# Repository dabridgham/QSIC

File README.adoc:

= QSIC - QBUS Storage and I/O Card

The QSIC is a QBUS card with an FPGA and SD cards that emulates the old DEC disk
controllers and drives.

This repository is the KiCad project for the hardware, the QSIC board
itself.  In addition there are separate projects for a Unibus version
of the board, the http://github.com/dabridgham/USIC[USIC], the
http://github.com/dabridgham/QSIC-Verilog[Verilog code] that runs on
the FPGAs, and the code that runs on the embedded soft processor (not
yet started).

A companion http://github.com/dabridgham/Indicator-Panel[indicator
panel] is also available for those who want the blinkenlights.

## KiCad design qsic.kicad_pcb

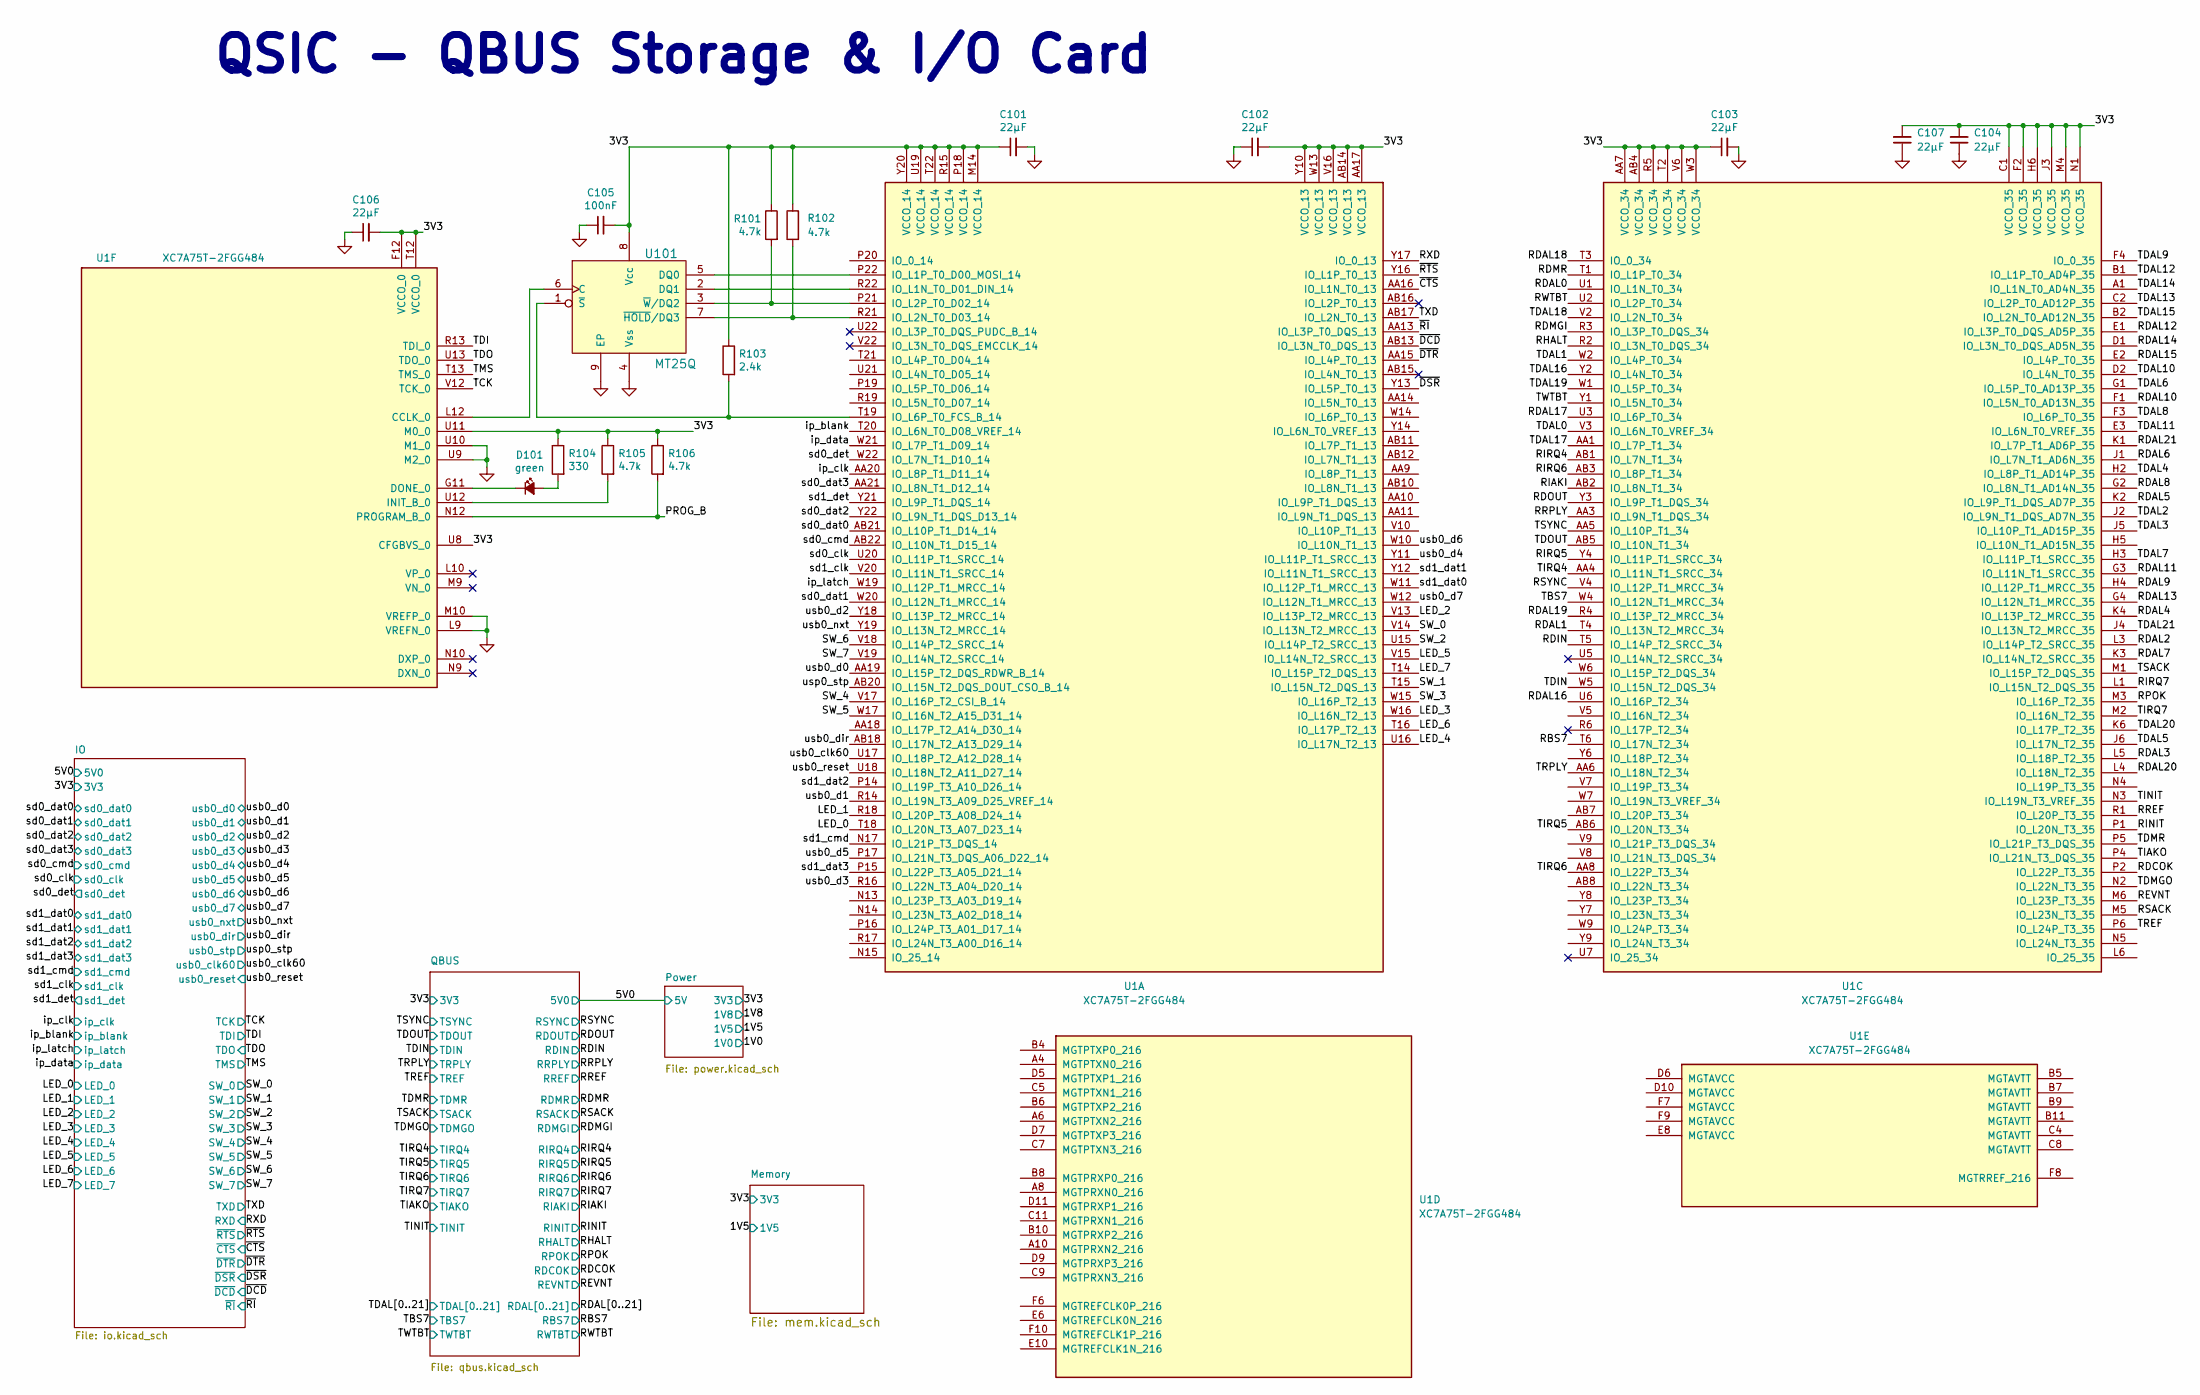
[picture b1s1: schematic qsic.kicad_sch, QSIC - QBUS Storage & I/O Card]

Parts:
C101, C102, C103, C104, C106, C107: 22µF; C_0603_1608Metric; MPN CL10A226MP8NUNE; JLCPCB Part C59461
C105: 100nF; C_0603_1608Metric; MPN CL10B104KO8NNNC
D101: green; LED_0603_1608Metric; MPN LTST-C190KGKT; JLCPCB Part C2297
R101, R102, R105, R106: 4.7k; R_0603_1608Metric; MPN RC0603FR-074K7L
R103: 2.4k; R_0603_1608Metric; MPN RC0603FR-072K4L
R104: 330; R_0603_1608Metric; MPN RC0603FR-07330RL
U1: XC7A75T-2FGG484; Xilinx_FGG484
U101: MT25Q; DFN-8-1EP_6x5mm_P1.27mm_EP4x4mm; MPN MT25QL128ABA1EW7-0SIT

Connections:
/3V3: C101.1, C102.2, C103.1, C104.2, C105.2, C106.2, C107.2, R101.1, R102.1, R103.1, R104.1, R105.1, R106.1, U1.AA7 (VCCO_34), U1.AA17 (VCCO_13), U1.AB4 (VCCO_34), U1.AB14 (VCCO_13), U1.C1 (VCCO_35), U1.F2 (VCCO_35), U1.F12 (VCCO_0), U1.H6 (VCCO_35), U1.J3 (VCCO_35), U1.M4 (VCCO_35), U1.M14 (VCCO_14), U1.N1 (VCCO_35), U1.P18 (VCCO_14), U1.R5 (VCCO_34), U1.R15 (VCCO_14), U1.T2 (VCCO_34), U1.T12 (VCCO_0), U1.T22 (VCCO_14), U1.U8 (CFGBVS_0), U1.U11 (M0_0), U1.U19 (VCCO_14), U1.V6 (VCCO_34), U1.V16 (VCCO_13), U1.W3 (VCCO_34), U1.W13 (VCCO_13), U1.Y10 (VCCO_13), U1.Y20 (VCCO_14), U101.8 (Vcc); also elsewhere on the board
/LED_0: U1.T18 (IO_L20N_T3_A07_D23_14); also elsewhere on the board
/LED_1: U1.R18 (IO_L20P_T3_A08_D24_14); also elsewhere on the board
/LED_2: U1.V13 (IO_L13P_T2_MRCC_13); also elsewhere on the board
/LED_3: U1.W16 (IO_L16N_T2_13); also elsewhere on the board
/LED_4: U1.U16 (IO_L17N_T2_13); also elsewhere on the board
/LED_5: U1.V15 (IO_L14N_T2_SRCC_13); also elsewhere on the board
/LED_6: U1.T16 (IO_L17P_T2_13); also elsewhere on the board
/LED_7: U1.T14 (IO_L15P_T2_DQS_13); also elsewhere on the board
/PROG_B: R106.2, U1.N12 (PROGRAM_B_0)
/RBS7: U1.T6 (IO_L17N_T2_34); also elsewhere on the board
/RDAL0: U1.U1 (IO_L1N_T0_34); also elsewhere on the board
/RDAL1: U1.T4 (IO_L13N_T2_MRCC_34); also elsewhere on the board
/RDAL2: U1.L3 (IO_L14P_T2_SRCC_35); also elsewhere on the board
/RDAL3: U1.L5 (IO_L18P_T2_35); also elsewhere on the board
/RDAL4: U1.K4 (IO_L13P_T2_MRCC_35); also elsewhere on the board
/RDAL5: U1.K2 (IO_L9P_T1_DQS_AD7P_35); also elsewhere on the board
/RDAL6: U1.J1 (IO_L7N_T1_AD6N_35); also elsewhere on the board
/RDAL7: U1.K3 (IO_L14N_T2_SRCC_35); also elsewhere on the board
/RDAL8: U1.G2 (IO_L8N_T1_AD14N_35); also elsewhere on the board
/RDAL9: U1.H4 (IO_L12P_T1_MRCC_35); also elsewhere on the board
/RDAL10: U1.F1 (IO_L5N_T0_AD13N_35); also elsewhere on the board
/RDAL11: U1.G3 (IO_L11N_T1_SRCC_35); also elsewhere on the board
/RDAL12: U1.E1 (IO_L3P_T0_DQS_AD5P_35); also elsewhere on the board
/RDAL13: U1.G4 (IO_L12N_T1_MRCC_35); also elsewhere on the board
/RDAL14: U1.D1 (IO_L3N_T0_DQS_AD5N_35); also elsewhere on the board
/RDAL15: U1.E2 (IO_L4P_T0_35); also elsewhere on the board
/RDAL16: U1.U6 (IO_L16P_T2_34); also elsewhere on the board
/RDAL17: U1.U3 (IO_L6P_T0_34); also elsewhere on the board
/RDAL18: U1.T3 (IO_0_34); also elsewhere on the board
/RDAL19: U1.R4 (IO_L13P_T2_MRCC_34); also elsewhere on the board
/RDAL20: U1.L4 (IO_L18N_T2_35); also elsewhere on the board
/RDAL21: U1.K1 (IO_L7P_T1_AD6P_35); also elsewhere on the board
/RDCOK: U1.P2 (IO_L22P_T3_35); also elsewhere on the board
/RDIN: U1.T5 (IO_L14P_T2_SRCC_34); also elsewhere on the board
/RDMGI: U1.R3 (IO_L3P_T0_DQS_34); also elsewhere on the board
/RDMR: U1.T1 (IO_L1P_T0_34); also elsewhere on the board
/RDOUT: U1.Y3 (IO_L9P_T1_DQS_34); also elsewhere on the board
/REVNT: U1.M6 (IO_L23P_T3_35); also elsewhere on the board
/RHALT: U1.R2 (IO_L3N_T0_DQS_34); also elsewhere on the board
/RIAKI: U1.AB2 (IO_L8N_T1_34); also elsewhere on the board
/RINIT: U1.P1 (IO_L20N_T3_35); also elsewhere on the board
/RIRQ4: U1.AB1 (IO_L7N_T1_34); also elsewhere on the board
/RIRQ5: U1.Y4 (IO_L11P_T1_SRCC_34); also elsewhere on the board
/RIRQ6: U1.AB3 (IO_L8P_T1_34); also elsewhere on the board
/RIRQ7: U1.L1 (IO_L15N_T2_DQS_35); also elsewhere on the board
/RPOK: U1.M3 (IO_L16P_T2_35); also elsewhere on the board
/RREF: U1.R1 (IO_L20P_T3_35); also elsewhere on the board
/RRPLY: U1.AA3 (IO_L9N_T1_DQS_34); also elsewhere on the board
/RSACK: U1.M5 (IO_L23N_T3_35); also elsewhere on the board
/RSYNC: U1.V4 (IO_L12P_T1_MRCC_34); also elsewhere on the board
/RWTBT: U1.U2 (IO_L2P_T0_34); also elsewhere on the board
/RXD: U1.Y17 (IO_0_13); also elsewhere on the board
/SW_0: U1.V14 (IO_L13N_T2_MRCC_13); also elsewhere on the board
/SW_1: U1.T15 (IO_L15N_T2_DQS_13); also elsewhere on the board
/SW_2: U1.U15 (IO_L14P_T2_SRCC_13); also elsewhere on the board
/SW_3: U1.W15 (IO_L16P_T2_13); also elsewhere on the board
/SW_4: U1.V17 (IO_L16P_T2_CSI_B_14); also elsewhere on the board
/SW_5: U1.W17 (IO_L16N_T2_A15_D31_14); also elsewhere on the board
/SW_6: U1.V18 (IO_L14P_T2_SRCC_14); also elsewhere on the board
/SW_7: U1.V19 (IO_L14N_T2_SRCC_14); also elsewhere on the board
/TBS7: U1.W4 (IO_L12N_T1_MRCC_34); also elsewhere on the board
/TCK: U1.V12 (TCK_0); also elsewhere on the board
/TDAL0: U1.V3 (IO_L6N_T0_VREF_34); also elsewhere on the board
/TDAL1: U1.W2 (IO_L4P_T0_34); also elsewhere on the board
/TDAL2: U1.J2 (IO_L9N_T1_DQS_AD7N_35); also elsewhere on the board
/TDAL3: U1.J5 (IO_L10P_T1_AD15P_35); also elsewhere on the board
/TDAL4: U1.H2 (IO_L8P_T1_AD14P_35); also elsewhere on the board
/TDAL5: U1.J6 (IO_L17N_T2_35); also elsewhere on the board
/TDAL6: U1.G1 (IO_L5P_T0_AD13P_35); also elsewhere on the board
/TDAL7: U1.H3 (IO_L11P_T1_SRCC_35); also elsewhere on the board
/TDAL8: U1.F3 (IO_L6P_T0_35); also elsewhere on the board
/TDAL9: U1.F4 (IO_0_35); also elsewhere on the board
/TDAL10: U1.D2 (IO_L4N_T0_35); also elsewhere on the board
/TDAL11: U1.E3 (IO_L6N_T0_VREF_35); also elsewhere on the board
/TDAL12: U1.B1 (IO_L1P_T0_AD4P_35); also elsewhere on the board
/TDAL13: U1.C2 (IO_L2P_T0_AD12P_35); also elsewhere on the board
/TDAL14: U1.A1 (IO_L1N_T0_AD4N_35); also elsewhere on the board
/TDAL15: U1.B2 (IO_L2N_T0_AD12N_35); also elsewhere on the board
/TDAL16: U1.Y2 (IO_L4N_T0_34); also elsewhere on the board
/TDAL17: U1.AA1 (IO_L7P_T1_34); also elsewhere on the board
/TDAL18: U1.V2 (IO_L2N_T0_34); also elsewhere on the board
/TDAL19: U1.W1 (IO_L5P_T0_34); also elsewhere on the board
/TDAL20: U1.K6 (IO_L17P_T2_35); also elsewhere on the board
/TDAL21: U1.J4 (IO_L13N_T2_MRCC_35); also elsewhere on the board
/TDI: U1.R13 (TDI_0); also elsewhere on the board
/TDIN: U1.W5 (IO_L15N_T2_DQS_34); also elsewhere on the board
/TDMGO: U1.N2 (IO_L22N_T3_35)
/TDMR: U1.P5 (IO_L21P_T3_DQS_35); also elsewhere on the board
/TDO: U1.U13 (TDO_0); also elsewhere on the board
/TDOUT: U1.AB5 (IO_L10N_T1_34); also elsewhere on the board
/TIAKO: U1.P4 (IO_L21N_T3_DQS_35); also elsewhere on the board
/TINIT: U1.N3 (IO_L19N_T3_VREF_35); also elsewhere on the board
/TIRQ4: U1.AA4 (IO_L11N_T1_SRCC_34); also elsewhere on the board
/TIRQ5: U1.AB6 (IO_L20N_T3_34); also elsewhere on the board
/TIRQ6: U1.AA8 (IO_L22P_T3_34); also elsewhere on the board
/TIRQ7: U1.M2 (IO_L16N_T2_35); also elsewhere on the board
/TMS: U1.T13 (TMS_0); also elsewhere on the board
/TREF: U1.P6 (IO_L24P_T3_35)
/TRPLY: U1.AA6 (IO_L18N_T2_34); also elsewhere on the board
/TSACK: U1.M1 (IO_L15P_T2_DQS_35); also elsewhere on the board
/TSYNC: U1.AA5 (IO_L10P_T1_34); also elsewhere on the board
/TWTBT: U1.Y1 (IO_L5N_T0_34); also elsewhere on the board
/TXD: U1.AB17 (IO_L2N_T0_13); also elsewhere on the board
/ip_blank: U1.T20 (IO_L6N_T0_D08_VREF_14); also elsewhere on the board
/ip_clk: U1.AA20 (IO_L8P_T1_D11_14); also elsewhere on the board
/ip_data: U1.W21 (IO_L7P_T1_D09_14); also elsewhere on the board
/ip_latch: U1.W19 (IO_L12P_T1_MRCC_14); also elsewhere on the board
/sd0_clk: U1.U20 (IO_L11P_T1_SRCC_14); also elsewhere on the board
/sd0_cmd: U1.AB22 (IO_L10N_T1_D15_14); also elsewhere on the board
/sd0_dat0: U1.AB21 (IO_L10P_T1_D14_14); also elsewhere on the board
/sd0_dat1: U1.W20 (IO_L12N_T1_MRCC_14); also elsewhere on the board
/sd0_dat2: U1.Y22 (IO_L9N_T1_DQS_D13_14); also elsewhere on the board
/sd0_dat3: U1.AA21 (IO_L8N_T1_D12_14); also elsewhere on the board
/sd0_det: U1.W22 (IO_L7N_T1_D10_14); also elsewhere on the board
/sd1_clk: U1.V20 (IO_L11N_T1_SRCC_14); also elsewhere on the board
/sd1_cmd: U1.N17 (IO_L21P_T3_DQS_14); also elsewhere on the board
/sd1_dat0: U1.W11 (IO_L12P_T1_MRCC_13); also elsewhere on the board
/sd1_dat1: U1.Y12 (IO_L11N_T1_SRCC_13); also elsewhere on the board
/sd1_dat2: U1.P14 (IO_L19P_T3_A10_D26_14); also elsewhere on the board
/sd1_dat3: U1.P15 (IO_L22P_T3_A05_D21_14); also elsewhere on the board
/sd1_det: U1.Y21 (IO_L9P_T1_DQS_14); also elsewhere on the board
/usb0_clk60: U1.U17 (IO_L18P_T2_A12_D28_14); also elsewhere on the board
/usb0_d0: U1.AA19 (IO_L15P_T2_DQS_RDWR_B_14); also elsewhere on the board
/usb0_d1: U1.R14 (IO_L19N_T3_A09_D25_VREF_14); also elsewhere on the board
/usb0_d2: U1.Y18 (IO_L13P_T2_MRCC_14); also elsewhere on the board
/usb0_d3: U1.R16 (IO_L22N_T3_A04_D20_14); also elsewhere on the board
/usb0_d4: U1.Y11 (IO_L11P_T1_SRCC_13); also elsewhere on the board
/usb0_d5: U1.P17 (IO_L21N_T3_DQS_A06_D22_14); also elsewhere on the board
/usb0_d6: U1.W10 (IO_L10N_T1_13); also elsewhere on the board
/usb0_d7: U1.W12 (IO_L12N_T1_MRCC_13); also elsewhere on the board
/usb0_dir: U1.AB18 (IO_L17N_T2_A13_D29_14); also elsewhere on the board
/usb0_nxt: U1.Y19 (IO_L13N_T2_MRCC_14); also elsewhere on the board
/usb0_reset: U1.U18 (IO_L18N_T2_A11_D27_14); also elsewhere on the board
/usp0_stp: U1.AB20 (IO_L15N_T2_DQS_DOUT_CSO_B_14); also elsewhere on the board
/~CTS: U1.AA16 (IO_L1N_T0_13); also elsewhere on the board
/~DCD: U1.AB13 (IO_L3N_T0_DQS_13); also elsewhere on the board
/~DSR: U1.Y13 (IO_L5P_T0_13); also elsewhere on the board
/~DTR: U1.AA15 (IO_L4P_T0_13); also elsewhere on the board
/~RI: U1.AA13 (IO_L3P_T0_DQS_13); also elsewhere on the board
/~RTS: U1.Y16 (IO_L1P_T0_13); also elsewhere on the board
GND: C101.2, C102.1, C103.2, C104.1, C105.1, C106.1, C107.1, U1.L9 (VREFN_0), U1.M10 (VREFP_0), U1.U9 (M2_0), U1.U10 (M1_0), U101.4 (Vss), U101.9 (EP); also elsewhere on the board
unnamed: D101.2 (A), R104.2
unnamed: D101.1 (K), U1.G11 (DONE_0)
unnamed: R105.2, U1.U12 (INIT_B_0)
unnamed: U1.L12 (CCLK_0), U101.6 (C)
unnamed: U1.P22 (IO_L1P_T0_D00_MOSI_14), U101.5 (DQ0)
unnamed: U1.R22 (IO_L1N_T0_D01_DIN_14), U101.2 (DQ1)
unnamed: R102.2, U1.R21 (IO_L2N_T0_D03_14), U101.7 (~HOLD/DQ3)
unnamed: R103.2, U1.T19 (IO_L6P_T0_FCS_B_14), U101.1 (~S)
unnamed: R101.2, U1.P21 (IO_L2P_T0_D02_14), U101.3 (~W/DQ2)

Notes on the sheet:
QSIC - QBUS Storage & I/O Card

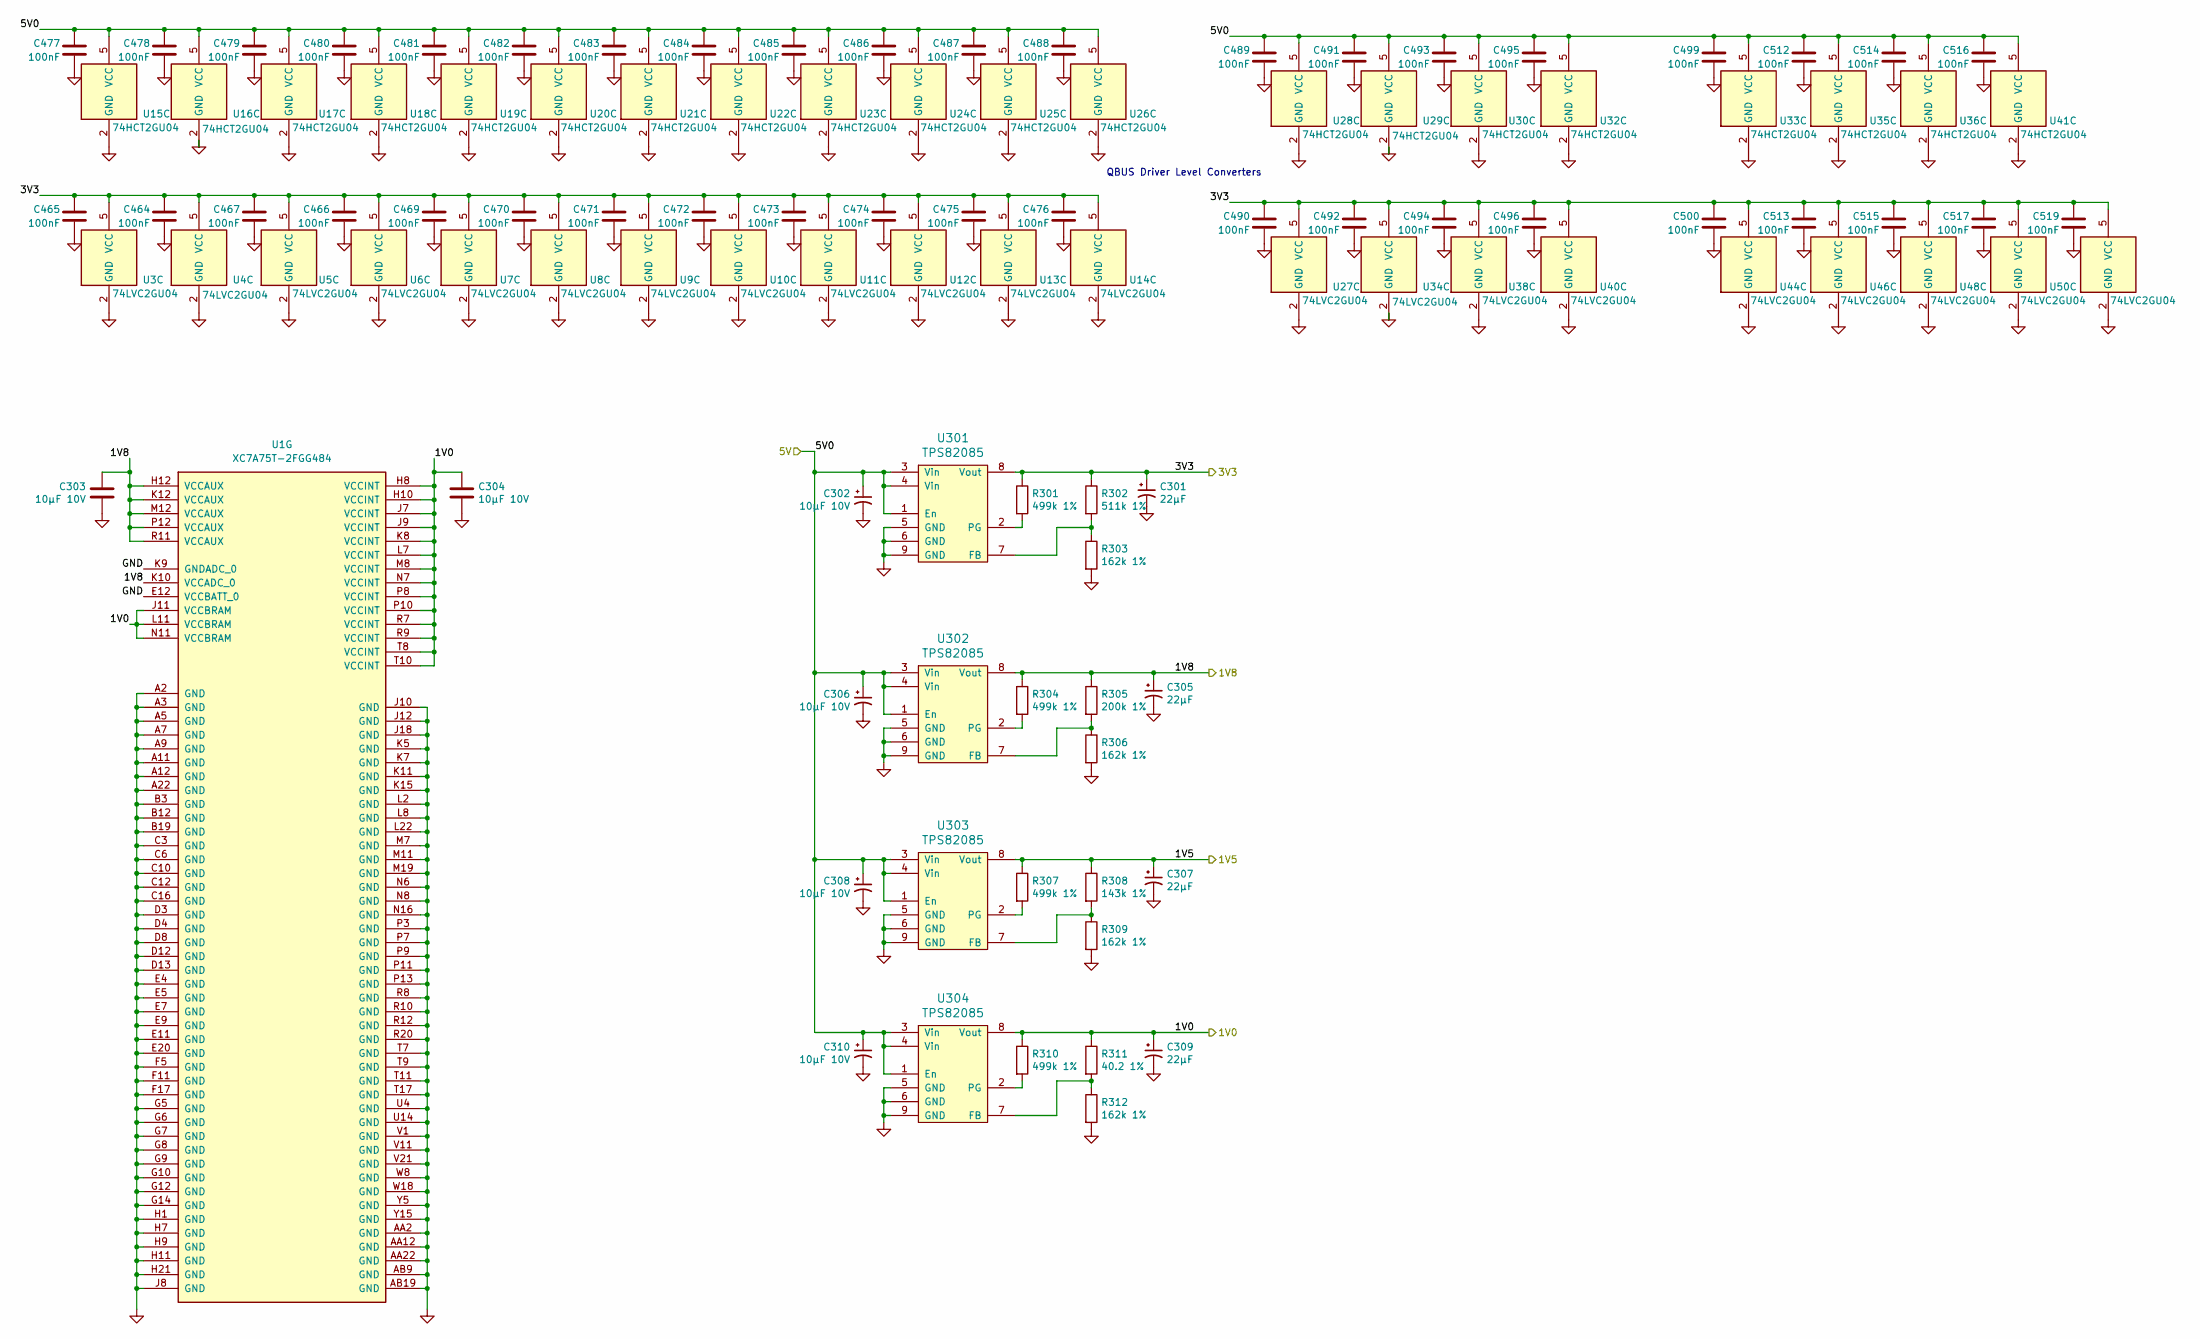
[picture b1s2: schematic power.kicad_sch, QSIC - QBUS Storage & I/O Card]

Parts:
C301, C305, C307, C309: 22µF; C_0603_1608Metric; MPN CL10A226MP8NUNE; JLCPCB Part C59461
C302, C303, C304, C306, C308, C310: 10µF 10V; C_0603_1608Metric; MPN CL10A106MP8NNNC; JLCPCB Part C85713
C464, C465, C466, C467, C469, C470, C471, C472, C473, C474, C475, C476, C477, C478, C479, C480, C481, C482, C483, C484, C485, C486, C487, C488, C489, C490, C491, C492, C493, C494, C495, C496, C499, C500, C512, C513, C514, C515, C516, C517, C519: 100nF; C_0402_1005Metric
R301, R304, R307, R310: 499k 1%; R_0603_1608Metric; MPN RC0603FR-07499KL; JLCPCB Part C131054
R302: 511k 1%; R_0603_1608Metric; MPN RC0603FR-07511KL; JLCPCB Part C188257
R303, R306, R309, R312: 162k 1%; R_0603_1608Metric; MPN RC0603FR-07162KL
R305: 200k 1%; R_0603_1608Metric; MPN RC0603FR-07200KL
R308: 143k 1%; R_0603_1608Metric; MPN RC0603FR-07143KL
R311: 40.2 1%; R_0603_1608Metric; MPN RC0603FR-0740R2L
U1: XC7A75T-2FGG484; Xilinx_FGG484
U3, U4, U5, U6, U7, U8, U9, U10, U11, U12, U13, U14, U27, U34, U38, U40, U44, U46, U48, U50, U52: 74LVC2GU04; SOT-363_SC-70-6
U15, U16, U17, U18, U19, U20, U21, U22, U23, U24, U25, U26, U28, U29, U30, U32, U33, U35, U36, U41: 74HCT2GU04; SOT-363_SC-70-6
U301, U302, U303, U304: TPS82085; Texas_SIL0008D_MicroSiP-8-1EP_2.8x3mm_P0.65mm_EP1.1x1.9mm_T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; MPN TPS82085SILT

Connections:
/1V0: C304.1, C309.1, R310.1, R311.1, U1.H8 (VCCINT), U1.H10 (VCCINT), U1.J7 (VCCINT), U1.J9 (VCCINT), U1.J11 (VCCBRAM), U1.K8 (VCCINT), U1.L7 (VCCINT), U1.L11 (VCCBRAM), U1.M8 (VCCINT), U1.N7 (VCCINT), U1.N11 (VCCBRAM), U1.P8 (VCCINT), U1.P10 (VCCINT), U1.R7 (VCCINT), U1.R9 (VCCINT), U1.T8 (VCCINT), U1.T10 (VCCINT), U304.8 (Vout)
/1V5: C307.1, R307.1, R308.1, U303.8 (Vout); also elsewhere on the board
/1V8: C303.1, C305.1, R304.1, R305.1, U1.H12 (VCCAUX), U1.K10 (VCCADC_0), U1.K12 (VCCAUX), U1.M12 (VCCAUX), U1.P12 (VCCAUX), U1.R11 (VCCAUX), U302.8 (Vout)
/3V3: C301.1, C464.1, C465.1, C466.1, C467.1, C469.1, C470.1, C471.1, C472.1, C473.1, C474.1, C475.1, C476.1, C490.1, C492.1, C494.1, C496.1, C500.1, C513.1, C515.1, C517.1, C519.1, R301.1, R302.1, U3.5 (VCC), U4.5 (VCC), U5.5 (VCC), U6.5 (VCC), U7.5 (VCC), U8.5 (VCC), U9.5 (VCC), U10.5 (VCC), U11.5 (VCC), U12.5 (VCC), U13.5 (VCC), U14.5 (VCC), U27.5 (VCC), U34.5 (VCC), U38.5 (VCC), U40.5 (VCC), U44.5 (VCC), U46.5 (VCC), U48.5 (VCC), U50.5 (VCC), U52.5 (VCC), U301.8 (Vout); also elsewhere on the board
/5V0: C302.1, C306.1, C308.1, C310.1, C477.1, C478.1, C479.1, C480.1, C481.1, C482.1, C483.1, C484.1, C485.1, C486.1, C487.1, C488.1, C489.1, C491.1, C493.1, C495.1, C499.1, C512.1, C514.1, C516.1, U15.5 (VCC), U16.5 (VCC), U17.5 (VCC), U18.5 (VCC), U19.5 (VCC), U20.5 (VCC), U21.5 (VCC), U22.5 (VCC), U23.5 (VCC), U24.5 (VCC), U25.5 (VCC), U26.5 (VCC), U28.5 (VCC), U29.5 (VCC), U30.5 (VCC), U32.5 (VCC), U33.5 (VCC), U35.5 (VCC), U36.5 (VCC), U41.5 (VCC), U301.1 (En), U301.3 (Vin), U301.4 (Vin), U302.1 (En), U302.3 (Vin), U302.4 (Vin), U303.1 (En), U303.3 (Vin), U303.4 (Vin), U304.1 (En), U304.3 (Vin), U304.4 (Vin); also elsewhere on the board
GND: C301.2, C302.2, C303.2, C304.2, C305.2, C306.2, C307.2, C308.2, C309.2, C310.2, C464.2, C465.2, C466.2, C467.2, C469.2, C470.2, C471.2, C472.2, C473.2, C474.2, C475.2, C476.2, C477.2, C478.2, C479.2, C480.2, C481.2, C482.2, C483.2, C484.2, C485.2, C486.2, C487.2, C488.2, C489.2, C490.2, C491.2, C492.2, C493.2, C494.2, C495.2, C496.2, C499.2, C500.2, C512.2, C513.2, C514.2, C515.2, C516.2, C517.2, C519.2, R303.2, R306.2, R309.2, R312.2, U1.A2 (GND), U1.A3 (GND), U1.A5 (GND), U1.A7 (GND), U1.A9 (GND), U1.A11 (GND), U1.A12 (GND), U1.A22 (GND), U1.AA2 (GND), U1.AA12 (GND), U1.AA22 (GND), U1.AB9 (GND), U1.AB19 (GND), U1.B3 (GND), U1.B12 (GND), U1.B19 (GND), U1.C3 (GND), U1.C6 (GND), U1.C10 (GND), U1.C12 (GND), U1.C16 (GND), U1.D3 (GND), U1.D4 (GND), U1.D8 (GND), U1.D12 (GND), U1.D13 (GND), U1.E4 (GND), U1.E5 (GND), U1.E7 (GND), U1.E9 (GND), U1.E11 (GND), U1.E12 (VCCBATT_0), U1.E20 (GND), U1.F5 (GND), U1.F11 (GND), U1.F17 (GND), U1.G5 (GND), U1.G6 (GND), U1.G7 (GND), U1.G8 (GND), U1.G9 (GND), U1.G10 (GND), U1.G12 (GND), U1.G14 (GND), U1.H1 (GND), U1.H7 (GND), U1.H9 (GND), U1.H11 (GND), U1.H21 (GND), U1.J8 (GND), U1.J10 (GND), U1.J12 (GND), U1.J18 (GND), U1.K5 (GND), U1.K7 (GND), U1.K9 (GNDADC_0), U1.K11 (GND), U1.K15 (GND), U1.L2 (GND), U1.L8 (GND), U1.L22 (GND), U1.M7 (GND), U1.M11 (GND), U1.M19 (GND), U1.N6 (GND), U1.N8 (GND), U1.N16 (GND), U1.P3 (GND), U1.P7 (GND), U1.P9 (GND), U1.P11 (GND), U1.P13 (GND), U1.R8 (GND), U1.R10 (GND), U1.R12 (GND), U1.R20 (GND), U1.T7 (GND), U1.T9 (GND), U1.T11 (GND), U1.T17 (GND), U1.U4 (GND), U1.U14 (GND), U1.V1 (GND), U1.V11 (GND), U1.V21 (GND), U1.W8 (GND), U1.W18 (GND), U1.Y5 (GND), U1.Y15 (GND), U3.2 (GND), U4.2 (GND), U5.2 (GND), U6.2 (GND), U7.2 (GND), U8.2 (GND), U9.2 (GND), U10.2 (GND), U11.2 (GND), U12.2 (GND), U13.2 (GND), U14.2 (GND), U15.2 (GND), U16.2 (GND), U17.2 (GND), U18.2 (GND), U19.2 (GND), U20.2 (GND), U21.2 (GND), U22.2 (GND), U23.2 (GND), U24.2 (GND), U25.2 (GND), U26.2 (GND), U27.2 (GND), U28.2 (GND), U29.2 (GND), U30.2 (GND), U32.2 (GND), U33.2 (GND), U34.2 (GND), U35.2 (GND), U36.2 (GND), U38.2 (GND), U40.2 (GND), U41.2 (GND), U44.2 (GND), U46.2 (GND), U48.2 (GND), U50.2 (GND), U52.2 (GND), U301.5 (GND), U301.6 (GND), U301.9 (GND), U302.5 (GND), U302.6 (GND), U302.9 (GND), U303.5 (GND), U303.6 (GND), U303.9 (GND), U304.5 (GND), U304.6 (GND), U304.9 (GND); also elsewhere on the board
unnamed: R302.2, R303.1, U301.7 (FB)
unnamed: R301.2, U301.2 (PG)
unnamed: R305.2, R306.1, U302.7 (FB)
unnamed: R304.2, U302.2 (PG)
unnamed: R308.2, R309.1, U303.7 (FB)
unnamed: R307.2, U303.2 (PG)
unnamed: R311.2, R312.1, U304.7 (FB)
unnamed: R310.2, U304.2 (PG)

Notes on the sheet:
QBUS Driver Level Converters
